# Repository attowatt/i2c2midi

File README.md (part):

# i2c2midi

### i2c2midi is a DIY open source 2 HP Teletype Expander that speaks I2C and MIDI.

i2c2midi bridges the gap between [monome Teletype](https://monome.org/docs/teletype/) and external MIDI-enabled devices. Using dedicated Teletype OPs, i2c2midi adds MIDI in and out to Teletype.

→ MIDI out:  
Sends MIDI notes, MIDI CC messages and other MIDI messages from Teletype to external devices like synths and effects.  

← MIDI in:  
Receives MIDI messages from external MIDI controllers and stores the values internally, which can be requested and used within Teletype.

- Dedicated Teletype OPs: `I2M.x`
- MIDI *out* via TRS
- MIDI *out* and *in* via USB Host
- Automatic MIDI Note Off messages (settable note duration per note)
- Chords and Chord Transformations
- Looping MIDI buffer / MIDI recorder
- Works with monome crow, too, thanks to [mreid](https://github.com/mreid/crow-i2c2midi)  
- 8 voice polyphony per MIDI channel, 16 channels simultaneously
- 2 HP, 42 mm depth

i2c2midi lines community thread:   
https://llllllll.co/t/i2c2midi-a-diy-module-that-translates-i2c-to-midi/

<br/>

<br/><br/>

## Table of contents
[Connections](#connections)  
[Example Scripts](#example-scripts)  
[Teletype OPs](#teletype-ops)   
[Further Reading](#further-reading)   
[Build the module](#build-the-module)  
[Firmware](#firmware)  
[crow Library](#crow-library)  
[Thanks](#thanks)  
[Sources](#sources)  

<br/><br/>

## Connections

### TRS

Use a TRS MIDI adapter (Type A) to connect a standard MIDI DIN cable to the TRS output of i2c2midi.

i2c2midi can be used with up to 16 different external MIDI-enabled devices simultaneously, with each device receiving MIDI messages on one of the 16 available MIDI channels. Just make sure each device is set to a different MIDI channel. Use a MIDI through splitter to connect all devices. Set the MIDI channel to 1..16 for the TRS output, using `I2M.CH`.

Please note: The TRS connection is MIDI *out* only!

### USB 

The USB connection can be used for either [MIDI *out*](#usb-midi-out-host) to connect an additional device (e.g. Teenage Engineering OP-1), or [MIDI *in*](#usb-midi-in-host) to receive MIDI Note or CC messages from an external MIDI controller.

Several MIDI controllers can be connected using a USB hub for MIDI *in*.

i2c2midi acts as a USB host, which makes it possible to connect external USB devices without the need of a computer. However, this also means that a computer (which acts as a host itself) can not be connected via the USB A jack on the front panel. However, it is possible to connect a USB host via the Micro USB jack of the Teensy. [More info about that here](#usb-midi-out-device-to-host).

#### USB MIDI out (Host)

The USB MIDI out connection works like the TRS output, but the 16 available MIDI channels can be addressed separately from TRS. Set the MIDI channel with `I2M.CH` to 17..32 for MIDI channels 1..16 on the USB connection. Please note: Only one USB device can be connected at a time.

#### USB MIDI in (Host)

If an external MIDI controller is connected via USB, incoming MIDI messages are stored internally in i2c2midi, and can be requested by Teletype at any time:

 - MIDI Note messages: The last eight notes and their velocities are stored in a rotating "note history". Each new received note gets added to the history and pushes the oldest note out. The notes and velocities can be requested with `I2M.Q.N` and `I2M.Q.V`.
 - MIDI CC messages: All values (127 controllers * 16 channels = 2032 values total) are stored and can be requested with `I2M.Q.CC`.

**Please note: Use external power or a powered USB hub!**

If you connect a MIDI device without its own power supply, use a powered USB hub with power supply in between i2c2midi and the MIDI device. This prevents too much current from being drawn from the Teensy and the voltage regulator on the PCB. I would advise to always use a powered USB hub in between – to be on the safe side. 

In case of OP-1, please turn off USB charging by pressing `shift` + `COM`, then `OPT` (T4), then turn the blue encoder to toggle USB charging off.

#### USB MIDI out (Device to Host)

i2c2midi can act as a USB device, too, if you want to connect a device that acts as a USB host (e.g. a computer). For this, you can use the Micro USB jack of the Teensy, which is accessible on the back of the module. Enable the `USB_DEVICE` feature flag in the firmware (look for `//#define USB_DEVICE` and remove the `//`). 
Most importantly: Cut the 5V pads on the Teensy! Otherwise you will damage your Teensy once you connect power from the modular and the host device on the USB port. For more info on why and how to cut the 5V pads, please follow [this link](https://www.pjrc.com/teensy/external_power.html).

**Please note: Don't connect power and USB at the same time!**

Caution: Do not connect power from the modular and the default USB port of the Teensy at the same time, unless you have cut the 5V pads on the Teensy!! Otherwise you will damage your Teensy. 

### LEDs

- The top LED lights up when MIDI messages are coming in.
- The bottom LED lights up when MIDI messages are going out.

<br/>

<br/><br/>

---

## Example Scripts

#### Play a random note
```
#1 
I2M.CH 1                // set channel to 1
I2M.N + 60 RND 24 127   // play note between 60 and 84
```

#### Play a V/Oct note using `VN`
```
#1
J N.B RRND 1 15         // random note from a scale in V/Oct
K VN J                  // convert the V/Oct value to MIDI note number
I2M.N + 60 K 127        // play note 
```

#### Define and play a chord
```
#1
I2M.C.CLR 1             // clear chord 1
I2M.C.ADD 1 0           // add relative note 0
I2M.C.ADD 1 3           // add relative note 3
I2M.C.ADD 1 7           // add relative note 7

#2
I2M.C.STR 1 100         // set strumming to 100
I2M.C.DIR 1 7           // set play direction to 7: Pingpong
I2M.C 1 60 127          // play chord 1 with rootnote 60 and velocity 127 (= 60,63,67)
```

#### Define a chord using reverse binary
```
#1
I2M.C.B 1 R10010001     // define chord: 1 means add, 0 means don't add = 0,3,7
I2M.C 1 60 127          // play chord 1 with rootnote 60 and velocity 127 (= 60,63,67)
```

#### Play chords stored in pattern 0
```
#1 
I2M.C.B 1 PN.NEXT 0     // define chord with next value in pattern 0
I2M.C 1 60 127          // play chord 1 with rootnote 60 and velocity 127

#Pattern 0
137                     // = R10010001    = 0,3,7
265                     // = R100100001   = 0,3,8
1064                    // = R00010100001 = 3,5,10
1060                    // = R00100100001 = 2,5,10
```

#### Use chord 2 as scale for a chord 1
```
#1
I2M.C.B 1 R100100011    // define chord 1 = 0,3,7,8 (alternatively use "393")
I2M.C.B 2 R10110101101  // define chord 2 = 0,2,3,5,7,8,10 (minor scale) (or "1453")
I2M.C.SC 1 2            // set chord 2 as scale for chord 1

#2
J WRP + J 1 0 7         // increment J and wrap around 0 and 7
I2M.C.STR 1 200         // set strumming for chord 1 to 200 ms
I2M.C.TRP 1 J           // transpose chord 1 by J
I2M.C 1 60 127          // play chord 1 with rootnote 60 and velocity 127
```

#### Send transformed chord notes to Just Friends or ER-301 

To Just Friends:
```
#I 
JF.MODE 1
JF.SHIFT N 0

#1
I2M.C.B 1 R100100011    // define chord 1 = 0,3,7,8
I2M.C.B 2 R10110101101  // define chord 2 = 0,2,3,5,7,8,10 (minor scale)
I2M.C.SC 1 2            // set chord 2 as scale for chord 1

#2
J WRP + J 1 0 4         // increment J and wrap around 4
I2M.C.DIS 1 J 2         // distort chord 1 by J at anchor point 2
I2M.C.VCUR 1 1 40 100   // set a linear (type 1) velocity curve from 40% to 100%

#3
EV 4: $ 2
J WRP + J 1 0 3         // increment J and wrap around chord length
X I2M.C.QN 1 0 J        // get chord note and store in X
Y I2M.C.QV 1 127 J      // get chord note velocity and store in Y
Z SCL 0 127 0 800 Y     // scale velocity from 0..127 to 0..800
JF.NOTE N X VV Z        // play on Just Friends
```

To ER-301:  

```
#3
J WRP + J 1 0 3                 // increment J and wrap around chord length
SC.CV 1 N I2M.C.QN 1 0 J        // send V/Oct to ER-301
SC.CV 2 VV I2M.C.QV 1 127 J     // send velocity to ER-301 (set Gain to 7.88)
SC.TR.P 1                       // send a trigger to ER-301 envelope
```

#### Query CC 1-4 and store values in Pattern 0
```
#1 
L 0 3: PN 0 I I2M.Q.CC + I 1
```

#### Query MIDI notes from controller

Arpeggiator that plays MIDI notes currently held down on a connected MIDI controller.  
CV 1 sends out the V/OCT and CV 2 sends out the velocity. 

```
#I
I2M.Q.LATCH 0           // setting to only store currently played MIDI notes

#M
$ 1

#1
J WRP + J 1 0 7         // counter from 0..7
CV 1 N - I2M.Q.N J 48   // query MIDI note number and subtract 4 octaves
CV 2 VV * 4 I2M.Q.V J   // query MIDI note velocity and scale to VV 0..508
```

---

## Teletype OPs

### Overview

| Type | OP                                             | Alias   | Channel-specific variant [(?)](#channel-specific-op-variants) | Function                    |
| ---- | ---------------------------------------------- | ------- | ----------------------------------------------------- | ----------------------------------- |
| get  | [I2M.CH](#i2mch)                               | I2M.#   |                                                       | Get current Channel                 |
|      | [I2M.CH channel](#i2mch)                       | I2M.#   |                                                       | Set current Channel                 |
| get  | [I2M.TIME](#i2mtime)                           | I2M.T   | [I2M.T# channel](#i2mt)                               | Get note duration                   |
|      | [I2M.TIME duration](#i2mtime)                  | I2M.T   | [I2M.T# channel duration](#i2mt)                      | Set note duration                   |
| get  | [I2M.SHIFT](#i2mshift)                         | I2M.S   | [I2M.S# channel](#i2ms)                               | Get note shift                      |
|      | [I2M.SHIFT semitones](#i2mshift)               | I2M.S   | [I2M.S# channel semitones](#i2ms)                     | Set note shift                      |
|      | [I2M.MIN note mode](#i2mmin)                   |         | [I2M.MIN# channel note mode](#i2mmin-1)               | Set minimum note                    |
|      | [I2M.MAX note mode](#i2mmax)                   |         | [I2M.MAX# channel note mode](#i2mmax-1)               | Set maximum note                    |
| get  | [I2M.REP](#i2mrep)                             |         | [I2M.REP# channel](#i2mrep-1)                         | Get note repetition                 |
|      | [I2M.REP repetitions](#i2mrep)                 |         | [I2M.REP# channel repetitions](#i2mrep-1)             | Set note repetition                 |
| get  | [I2M.RAT](#i2mrat)                             |         | [I2M.RAT# channel](#i2mrat-1)                         | Get note ratcheting                 |
|      | [I2M.RAT ratchets](#i2mrat)                    |         | [I2M.RAT# channel ratchets](#i2mrat-1)                | Set note ratcheting                 |
|      | [I2M.MUTE on/off](#i2mmute)                    |         | [I2M.MUTE# channel on/off](i2mmute-1)                 | Set channel mute state              |
|      | [I2M.SOLO on/off](#i2msolo)                    |         | [I2M.SOLO# channel on/off](i2msolo-2)                 | Set channel solo state              |
|      | [I2M.NOTE note velocity](#i2mnote)             | I2M.N   | [I2M.N# channel note velocity](#i2mn)                 | Send Note On                        |
|      | [I2M.NOTE.O note](#i2mnoteo)                   | I2M.NO  | [I2M.NO# channel note](#i2mno)                        | Send Note Off                       |
|      | [I2M.NT note velocity duration](#i2mnt)        |         | [I2M.NT# channel note velocity dur](#i2mnt-1)         | Send Note On with duration          |
|      | [I2M.CHORD chord rootnote velocity](#i2mchord) | I2M.C   | [I2M.C# channel chord rootnote vel](#i2mc)            | Play chord                          |
|      | [I2M.C.ADD chord note](#i2mcadd)               | I2M.C+  |                                                       | Add note to chord                   |
|      | [I2M.C.RM chord note](#i2mcrm)                 | I2M.C-  |                                                       | Remove note to chord                |
|      | [I2M.C.INS chord index note](#i2mcins)         |         |                                                       | Insert note at index                |
|      | [I2M.C.DEL chord index](#i2mcdel)              |         |                                                       | Delete note at index                |
|      | [I2M.C.SET chord index note](#i2mcset)         |         |                                                       | Set note at index                   |
|      | [I2M.C.B chord revbinary](#i2mcb)              |         |                                                       | Define chord using reverse binary   |
|      | [I2M.C.CLR chord](#i2mcclr)                    |         |                                                       | Clear chord                         |
| get  | [I2M.C.L chord](#i2mcl)                        |         |                                                       | Get chord length                    |
|      | [I2M.C.L chord length](#i2mcl)                 |         |                                                       | Set chord length                    |
|      | [I2M.C.SC chord1 chord2](#i2mcsc)              |         |                                                       | Set chord2 as scale for chord1      |
|      | [I2M.C.REV chord iterations](#i2mcrev)         |         |                                                       | Set chord reversal                  |
|      | [I2M.C.ROT chord iterations](#i2mcrot)         |         |                                                       | Set chord rotation                  |
|      | [I2M.C.TRP chord semitones](#i2mctrp)          |         |                                                       | Set chord transposition             |
|      | [I2M.C.DIS chord iter. anchorpoint](#i2mcdis)  |         |                                                       | Set chord distortion                |
|      | [I2M.C.REF chord iter. anchorpoint](#i2mcref)  |         |                                                       | Set chord reflection                |
|      | [I2M.C.INV chord iteration](#i2mcinv)          |         |                                                       | Set chord inversion                 |
|      | [I2M.C.STR chord ms](#i2mcstr)                 |         |                                                       | Set chord strumming                 |
|      | [I2M.C.VCUR chord curve start end](#i2mcvcur)  | I2M.V~  |                                                       | Set chord velocity curve            |
|      | [I2M.C.TCUR chord curve start end](#i2mctcur)  | I2M.T~  |                                                       | Set chord time curve                |
|      | [I2M.C.DIR chord direction](#i2mcdir)          |         |                                                       | Set chord play direction            |
|      | [I2M.C.QN chord rootnote index](#i2mcqn)       |         |                                                       | Query chord note at index           |
|      | [I2M.C.QV chord velocity index](#i2mcqv)       |         |                                                       | Query chord note velocity at index  |
|      | [I2M.B.R on/off](#i2mbr)                       |         |                                                       | Turn recording to buffer on/off     |
|      | [I2M.B.L length](#i2mbl)                       |         |                                                       | Set buffer length                   |
|      | [I2M.B.START offset](#i2mbstart)               |         |                                                       | Add offset to buffer start          |   
|      | [I2M.B.END offset](#i2mbend)                   |         |                                                       | Add a negative offset to buffer end | 
|      | [I2M.B.DIR direction](#i2mbdir)                |         |                                                       | Set buffer play direction           |    
|      | [I2M.B.SPE percent](#i2mbspe)                  |         |                                                       | Set buffer play speed               |
|      | [I2M.B.FB iterations](#i2mbfb)                 |         |                                                       | Iterations until velocity reaches 0 |
|      | [I2M.B.NSHIFT semitones](#i2mbnshift)          |         |                                                       | Set note shift                      |
|      | [I2M.B.VSHIFT velocity](#i2mbvshift)           |         |                                                       | Set velocity shift                  |
|      | [I2M.B.TSHIFT ms](#i2mbtshift)                 |         |                                                       | Set duration shift                  |
|      | [I2M.B.NOFF semitones](#i2mbnoff)              |         |                                                       | Set note offset                     |
|      | [I2M.B.VOFF velocity](#i2mbvoff)               |         |                                                       | Set velocity offset                 |
|      | [I2M.B.TOFF ms](#i2mbtoff)                     |         |                                                       | Set duration offset                 |
|      | [I2M.B.CLR](#i2mbclr)                          |         |                                                       | Clear the buffer                    |
|      | [I2M.B.MODE mode](#i2mbmode)                   |         |                                                       | Set buffer mode (Free, Tape)        |
|      | [I2M.CC controller value](#i2mcc)              |         | [I2M.CC# channel controller value](#i2mcc-1)          | Send CC                             |
|      | [I2M.CCV controller value](#i2mccv)            |         | [I2M.CCV# channel controller value](#i2mccv-1)        | Send CC with volt value             |
| get  | [I2M.CC.OFF controller](#i2mccoff)             |         | [I2M.CC.OFF# channel controller](#i2mccoff-1)         | Get CC offset                       |
|      | [I2M.CC.OFF controller offset](#i2mccoff)      |         | [I2M.CC.OFF# channel controller offset](#i2mccoff-1)  | Set CC offset                       |
| get  | [I2M.CC.SLEW controller](#i2mccslew)           |         | [I2M.CC.SLEW# channel controller](#i2mccslew-1)       | Get CC slew                         |
|      | [I2M.CC.SLEW controller ms](#i2mccslew)        |         | [I2M.CC.SLEW# channel controller ms](#i2mccslew-1)    | Set CC slew                         |
|      | [I2M.CC.SET controller value](#i2mccset)       |         | [I2M.CC.SET# channel controller value](#i2mccset-1)   | Send CC and ignore slew             |
|      | [I2M.NRPN msb lsb value](#i2mnrpn)             |         | [I2M.NRPN# channel msb lsb value](#i2mnrpn-1)         | Send NRPN                           |
| get  | [I2M.NRPN.OFF msb lsb](#i2mnrpnoff)            |         | [I2M.NRPN.OFF# channel msb lsb](#i2mnrpnoff-1)        | Get NRPN offset                     |
|      | [I2M.NRPN.OFF msb lsb offset](#i2mnrpnoff)     |         | [I2M.NRPN.OFF# channel msb lsb offset](#i2mnrpnoff-1) | Set NRPN offset                     |
| get  | [I2M.NRPN.SLEW msb lsb](#i2mnrpnslew)          |         | [I2M.NRPN.SLEW# channel msb lsb](#i2mnrpnslew-1)      | Get NRPN slew                       |
|      | [I2M.NRPN.SLEW msb lsb ms](#i2mnrpnslew)       |         | [I2M.NRPN.SLEW# channel msb lsb ms](#i2mnrpnslew-1)   | Set NRPN slew                       |
|      | [I2M.NRPN.SET msb lsb value](#i2mnrpnset)      |         | [I2M.NRPN.SET# value msb lsb value](#i2mnrpnset-1)    | Send NRPN and ignore slew           |
|      | [I2M.PRG program](#i2mprg)                     |         |                                                       | Send Program Change                 |
|      | [I2M.PB value](#i2mpb)                         |         |                                                       | Send Pitchbend                      |
|      | [I2M.AT value](#i2mat)                         |         |                                                       | Send Aftertouch                     |
|      | [I2M.CLK](#i2mclk)                             |         |                                                       | Send Clock                          |
|      | [I2M.START](#i2mstart)                         |         |                                                       | Send Clock Start                    |
|      | [I2M.STOP](#i2mstop)                           |         |                                                       | Send Clock Stop                     |
|      | [I2M.CONT](#i2mcont)                           |         |                                                       | Send Clock Continue                 |
| get  | [I2M.Q.CH](#i2mqch)                            |         |                                                       | Get current MIDI in Channel         |
|      | [I2M.Q.CH channel](#i2mqch)                    | I2M.Q.# |                                                       | Set current MIDI in Channel         |
|      | [I2M.Q.LATCH on/off](#i2mqlatch)               |         |                                                       | Turn latch on/off                   |
| get  | [I2M.Q.NOTE index](#i2mqnote)                  | I2M.Q.N |                                                       | Get x-last Note On                  |
| get  | [I2M.Q.VEL index](#i2mqvel)                    | I2M.Q.V |                                                       | Get x-last Velocity                 |
| get  | [I2M.Q.CC controller](#i2mqcc)                 |         |                                                       | Get CC value                        |
| get  | [I2M.Q.LCH](#i2mqlch)                          |         |                                                       | Get last MIDI in Channel            |
| get  | [I2M.Q.LN](#i2mqln)                            |         |                                                       | Get last MIDI in Note On            |
| get  | [I2M.Q.LV](#i2mqlv)                            |         |                                                       | Get last MIDI in Velocity           |
| get  | [I2M.Q.LO](#i2mqlo)                            |         |                                                       | Get last MIDI in Note Off           |
| get  | [I2M.Q.LC](#i2mqlc)                            |         |                                                       | Get last MIDI in Controller         |
| get  | [I2M.Q.LCC](#i2mqlcc)                          |         |                                                       | Get last MIDI in CC Value           |
|      | [I2M.PANIC](#i2mpanic)                         |         |                                                       | Don't panic!                        |

---

#### OP Name
`OP`  
`OP (set)`  
`Alias`    
Description  

---

### MIDI out: Settings
*Settings for outoing MIDI messages*  

#### I2M.CH
`I2M.CH`  
`I2M.CH x`  
`I2M.#`  

Get currently set MIDI channel / Set MIDI channel `x` (1..16 for TRS, 17..32 for USB) for MIDI out. Use MIDI channels 1-16 for TRS output, 17-32 for USB output. Default is `x = 1`.  

#### I2M.TIME
`I2M.TIME`  
`I2M.TIME x`  
`I2M.T`  

Get current note duration / Set note duration of MIDI notes to `x` ms (0..32767) for current channel. Based on note duration, i2c2midi will send a MIDI Note Off message automatically. Set `x = 0` to deactivate automatic Note Off messages. Default is `x = 100`.

#### I2M.T#
`I2M.T# ch`
`I2M.T# ch x`  

Get current note duration / Set note duration of MIDI notes to `x` ms (0..32767) for channel `ch` (0..32). Based on note duration, i2c2midi will send a MIDI Note Off message automatically. Set `x = 0` to deactivate automatic Note Off messages. Default is `x = 100`. Use `ch = 0` to set for all channels.

#### I2M.SHIFT
`I2M.SHIFT`  
`I2M.SHIFT x`  
`I2M.S`  

Get current transposition / Set transposition of MIDI notes to `x` semitones (-127..127) for current channel. Default is `x = 0`.  

#### I2M.S#
`I2M.S# ch`  
`I2M.S# ch x`  

Get current transposition / Set transposition of MIDI notes to `x` semitones (-127..127) for channel `ch` (0..32). Default is `x = 0`. Use `ch = 0` to set for all channels.  

#### I2M.MIN
`I2M.MIN x y`  

Set minimum note number of MIDI notes to `x` (0..127), using mode `y` (0..3), for current channel. Default is `x = 0` and `y = 0`. The following modes are available for notes lower than the minimum: 0) Ignore notes 1) Clamp notes 2) Fold back notes by one octave 3) Fold back notes by multiple octaves.  

#### I2M.MIN#
`I2M.MIN# ch x y`  

Set minimum note number of MIDI notes to `x` (0..127), using mode `y` (0..3), for channel `ch` (0..32). Default is `x = 0` and `y = 0`. The following modes are available for notes lower than the minimum: 0) Ignore notes 1) Clamp notes 2) Fold back notes by one octave 3) Fold back notes by multiple octaves. Use `ch = 0` to set for all channels.  

#### I2M.MAX
`I2M.MAX x y`  

Set maximum note number of MIDI notes to `x` (0..127), using mode `y` (0..3), for current channel. Default is `x = 0` and `y = 0`. The following modes are available for notes higher than the maximum: 0) Ignore notes 1) Clamp notes 2) Fold back notes by one octave 3) Fold back notes by multiple octaves. 

#### I2M.MAX#
`I2M.MAX# ch x y`  

Set maximum note number of MIDI notes to `x` (0..127), using mode `y` (0..3), for channel `ch` (0..32). Default is `x = 0` and `y = 0`. The following modes are available for notes higher than the maximum: 0) Ignore notes 1) Clamp notes 2) Fold back notes by one octave 3) Fold back notes by multiple octaves. Use `ch = 0` to set for all channels.  

#### I2M.REP
`I2M.REP`  
`I2M.REP x`  

Get current repetition / Set repetition of MIDI notes to `x` repetitions (1..127) for current channel. Set `x = 1` for no repetitions. Default is `x = 1`.  

#### I2M.REP#
`I2M.REP# ch`  
`I2M.REP# ch x`  

Get current repetition / Set repetition of MIDI notes to `x` repetitions (1..127) for channel `ch` (0..32). Set `x = 1` for no repetitions. Default is `x = 1`. Use `ch = 0` to set for all channels.  

#### I2M.RAT
`I2M.RAT`  
`I2M.RAT x`  

Get current ratcheting / Set ratcheting of MIDI notes to `x` ratchets (1..127) for current channel. Set `x = 1` for no ratcheting. Default is `x = 1`.  

#### I2M.RAT#
`I2M.RAT# ch`  
`I2M.RAT# ch x`  

Get current ratcheting / Set ratcheting of MIDI notes to `x` ratchets (1..127) for channel `ch` (0..32). Set `x = 1` for no ratcheting. Default is `x = 1`. Use `ch = 0` to set for all channels.  

#### I2M.MUTE
`I2M.MUTE x`  
  
Set mute state of current MIDI channel to `x`. If `x = 1` all outoing MIDI messages on that channel are muted. Default is `x = 0`.  

#### I2M.MUTE#
`I2M.MUTE# ch x`  
  
Set mute state of MIDI channel `ch` to `x`. If `x = 1` all outoing MIDI messages on that channel are muted. Default is `x = 0`. Use `ch = 0` to set for all channels.  

#### I2M.SOLO
`I2M.SOLO x`  

Set solo state of current MIDI channel to `x`. If `x = 1` all outoing MIDI messages on that channel are solod. Default is `x = 0`.  

#### I2M.SOLO#
`I2M.SOLO x`  

Set solo state of MIDI channel `ch` to `x`. If `x = 1` all outoing MIDI messages on that channel are solod. Default is `x = 0`. Use `ch = 0` to set for all channels.  

---

### MIDI out: Notes
*Send an individual MIDI note. Each note consists of a note number (pitch), velocity and duration. i2c2midi will take care of Note Off messages send an automatic Note Off message based on the set note duration. The note duration can be set globally via `I2M.TIME` or individually via `I2M.NT`.*  

#### I2M.NOTE
`I2M.NOTE x y`  
`I2M.N`  

Send MIDI Note On message for note number `x` (0..127) with velocity `y` (1..127) on current channel. A velocity of `0` will be treated as a MIDI Note Off message.  

#### I2M.N#
`I2M.N# ch x y`    

Send MIDI Note On message for note number `x` (0..127) with velocity `y` (1..127) on channel `ch` (1..32). A velocity of `0` will be treated as a MIDI Note Off message.

#### I2M.NOTE.O
`I2M.NOTE.O x`  
`I2M.NO`  

Send a manual MIDI Note Off message for note number `x` (0..127) on current channel. This can be used either before i2c2midi sends the automatic Note Off message (to stop the note from playing before its originally planned ending), or in combination with `I2M.TIME` set to `0` (in which case i2c2midi does not send automatic Note Off messages).

#### I2M.NO#
`I2M.NO# ch x`  

Send a manual MIDI Note Off message for note number `x` (0..127) on channel `ch` (1..32). This can be used either before i2c2midi sends the automatic Note Off message (to stop the note from playing before its originally planned ending), or in combination with `I2M.TIME` set to `0` (in which case i2c2midi does not send automatic Note Off messages).  

#### I2M.NT
`I2M.NT x y z`  

Send MIDI Note On message for note number `x` (0..127) with velocity `y` (1..127) and note duration `z` ms (0..32767) on current channel.   

#### I2M.NT#
`I2M.NT# ch x y z`  

Send MIDI Note On message for note number `x` (0..127) with velocity `y` (1..127) and note duration `z` ms (0..32767) on channel `ch` (1..32).    

---

### MIDI out: Chords
*Play a chord, consisting of multiple MIDI notes. Chords are basically groups of relative note numbers or pitches. One chord consists of up to eight notes defined via `I2M.C.ADD`, `I2M.C.RM`, `I2M.C.INS`, `I2M.C.DEL` or `I2M.C.SET`. The notes are defined relative to the root note which is specified when playing a chord via `I2M.C`. When a chord is played, the notes are sent out as individual MIDI notes in the order they are defined in the chord. If no note has been defined in the chord yet, no note will be played. 8 chords can be defined using their respective index 1..8.*

#### I2M.CHORD
`I2M.CHORD x y z`  
`I2M.C`  

Play chord `x` (1..8) with root note `y` (0..127) and velocity `z` (1..127) on current channel.  

#### I2M.C#
`I2M.C# ch x y z`  

Play chord `x` (1..8) with root note `y` (0..127) and velocity `z` (1..127) on channel `ch` (1..32).  

#### I2M.C.ADD
`I2M.C.ADD x y`  
`I2M.C+`  

Add note `y` (-127..127) to chord `x` (0..8), with `y` relative to the root note specified when playing a chord. E.g. add `0`, `4` and `7` to define a major triad. Or go more experimental, e.g. `-2`, `13`, `2`, `13`. Up to eight chords can be defined, with eight notes each. Use `x = 0` to add the note to all chords.  

#### I2M.C.RM
`I2M.C.RM x y`  
`I2M.C-`  

Remove note `y` (-127..127) from chord `x` (0..8). If the chord contains note `y` multiple times, the latest instance is removed. If the chord does not contain the note the message is simply ignored. Use `x = 0` to remove the note from all chords.  

#### I2M.C.INS
`I2M.C.INS x y z`  

Add note `z` (-127..127) to chord `x` (0..8) at index `y` (0..7), with `z` relative to the root note. Already defined notes at index `y` and higher are pushed to the right. Use `x = 0` to insert the note to all chords.  

#### I2M.C.DEL
`I2M.C.DEL x y`  

Delete note at index `y` (0..7) from chord `x` (0..8). Notes at index `y + 1` and higher are pushed to the left. If `y` is higher than the length of the chord, the message is ignored. Use `x = 0` to delete the note from all chords.  

#### I2M.C.SET
`I2M.C.SET x y z`  

Set note at index `y` (0..7) in chord `x` (0..8) to note `z` (-127..127), replacing what was defined earlier at this index. If `y` is higher than the length of the chord, the message is ignored. Use `x = 0` to set the note in all chords.  

#### I2M.C.B
`I2M.C.B x y`  

Clear and define chord `x` (0..8) using reverse binary notation (`R...`). Use `1` or `0` in order to include or exclude notes from the chord. E.g. use `x = R10001001` for `0,4,7` (major triad) or `x = R1000000100000001` for `0,7,15`. `y` can be a maximum of 16 digit long. Use `x = 0` to clear and define all chords.  

#### I2M.C.CLR
`I2M.C.CLR x`  

Clear chord `x` (0..8). Use `x = 0` to clear all chords.  

#### I2M.C.L
`I2M.C.L x`  
`I2M.C.L x y`  

Get current length / Set length of chord `x` (0..8) to `y` (1..8). The length of a chord changes automatically each time a note is added or removed. Values of `x` higher than number of actual defined notes are ignored. Already defined notes are not affected by setting the chord length, but won't be played if their index is outside of the set chord length. Use `x = 0` to set the length of all chords.  

#### I2M.C.SC
`I2M.C.SC x y`  

Set scale for chord `x` (0..8) based on chord `y` (0..8). Setting a scale for a chord comes in handy when using chord transformations that introduce new notes, like `I2M.C.TRP`, `I2M.C.DIS` or `I2M.C.REF`. Use `y = 0` to remove the scale. Use `x = 0` to set scale for all chords.    

→ [More info on how scales work on i2c2midi](#how-scales-work-on-i2c2midi)

#### I2M.C.REV
`I2M.C.REV x y`  

Set reversal of notes in chord `x` (0..8) to `y`. `y = 0` or an even number means not reversed, `y = 1` or an uneven number  means reversed. E.g. `y = 1` for chord `0,3,7` will lead to `7,3,0`. Default is `y = 0`. Use `x = 0` to set reversal all chords. 

  https://user-images.githubusercontent.com/76960718/170448152-c708c42d-ed18-4411-b0e5-6085a569185b.mp4

#### I2M.C.ROT
`I2M.C.ROT x y`  

Set rotation of notes in chord `x` (0..8) to `y` steps (-127..127). E.g. `y = 1` of chord `0,3,7` will lead to `3,7,0`, `y = 2` will lead to `7,0,3`, `y = -1` will lead to `7,0,3`. Default is `y = 0`. Use `x = 0` to set rotation for all chords.  

  https://user-images.githubusercontent.com/76960718/170448234-86cafa1e-8ecd-4612-9a84-febde5bead3d.mp4

#### I2M.C.TRP
`I2M.C.TRP x y`  

Set transposition of chord `x` (0..8) to `y` (-127..127). Transposition adds `y` to the note number of each note in the chord. Default is `y = 0`. Use `x = 0` to set transposition for all chords. This transformation introduces new notes to the chord – try it in combination with setting a scale.  

  https://user-images.githubusercontent.com/76960718/170448291-4766446c-830e-4b92-a609-74fe5c757047.mp4

#### I2M.C.DIS
`I2M.C.DIS x y z`  

Set distortion of chord `x` (0..8) to width `y` (-127..127) with anchor point `z` (0..16). Distortion adds `y+n` to the note number of each note in the chord. The anchor point influences the direction and amount (`n`) of the transformation. Default is `y = 0`. Use `x = 0` to set distortion for all chords. This transformation introduces new notes to the chord – try it in combination with setting a scale.  

  https://user-images.githubusercontent.com/76960718/170519200-57bbb0fd-a168-498a-873c-f39924235f2d.mp4

#### I2M.C.REF
`I2M.C.REF x y z`  

Set reflection of chord `x` (0..8) to `y` (-127..127) with anchor point `z` (0..16). The anchor point defines at which axis the chord gets reflected. Default is `y = 0`. Use `x = 0` to set distortion for all chords. This transformation introduces new notes to the chord – try it in combination with setting a scale.  

  https://user-images.githubusercontent.com/76960718/170448450-b01a0faa-ed1b-4541-b9ee-6c55721735cb.mp4

#### I2M.C.INV
`I2M.C.INV x y`  

Set inversion of chord `x` (0..8) to `y` (-32..32). Default is `y = 0`. Use `x = 0` to set inversion for all chords.  

  https://user-images.githubusercontent.com/76960718/170448519-62731788-977d-4e5f-a442-cc999a97c141.mp4

#### I2M.C.STR
`I2M.C.STR x y`  

Set strumming of chord `x` (0..8) to `y` ms (0..32767). Strumming plays the notes of a chord arpeggiated, with an interval of `y` ms in between notes. Default is `y = 0`. Use `x = 0` to set strumming for all chords.  

#### I2M.C.VCUR
`I2M.C.VCUR w x y z`  
`I2M.C.V~`  

Set velocity curve for chord `w` (0..8) with curve type `x` (0..5), start value `y`% (0..32767) and end value `z`% (0..32767). This will affect the velocity of the notes in the order they are defined in the chord. Start and end percentages refer to the velocity with which the chord is played via `I2M.C`. Use `x = 0` to turn velocity curve off. The following curves are available: 0) Off 1) Linear 2) Exponential 3) Triangle 4) Square 5) Random. Use `w = 0` to set velocity curve for all chords. Try a random curve with subtle values for a humanizing effect.  

#### I2M.C.TCUR
`I2M.C.TCUR w x y z`  
`I2M.C.T~`  

Set time curve for chord `w` (0..8) with curve type `x` (0..5), start value `y`% (0..32767) and end value `z`% (0..32767). This will affect the time interval between the notes in the order they are defined in the chord. Start and end percentages refer to the current strumming setting of the chord, set via `I2M.C.STR`. Use `x = 0` to turn time curve off. The following curves are available: 0) Off 1) Linear 2) Exponential 3) Triangle 4) Square 5) Random. Use `w = 0` to set time curve for all chords. Try a square curve with similar values to create swing. Try a random curve with subtle values for a humanizing effect.  

#### I2M.C.DIR
`I2M.C.DIR x y`   

Set play direction for chord `x` (0..8) to direction `y` (0..8). This will affect the order in which chord notes are played. Make sure to set strumming via `I2M.C.STR`. The following directions are available: 0) Forward (0,1,2,3,4) 1) Backward (4,3,2,1,0) 2) Inside out (2,1,3,0,4) 3) Outside in (0,4,1,3,2) 4) Random (2,3,1,0,4) 5) Bottom repeat (0,1,0,2,0,3,0,4) 6) Top repeat (0,4,1,4,2,4,3,4) 7) Pingpong (0,1,2,3,4,3,2,1,0) 8) Ping & pong (0,1,2,3,4,4,3,2,1,0). Default is `y = 0`.

#### I2M.C.QN
`I2M.C.QN x y z`   

Get the transformed note number of a chord note for chord `x` (1..8) with root note `y` (0..127) at index `z` (0..7). The reponse is the absolute note number (0..127). Use this OP to send the transformed note number to other devices within eurorack, e.g. via V/OCT to any oscillator or via I2C to I2C-enabled devices like Just Friends or disting EX.

#### I2M.C.QV
`I2M.C.QV x y z`   

Get the transformed note velocity of a chord note for chord `x` (1..8) with root velocity `y` (1..127) at index `z` (0..7). The response is the absolute note velocity (0..127). Use this OP to send the transformed note velocity to other devices within eurorack, e.g. via CV to a VCA or via I2C to I2C-enabled devices like Just Friends or disting EX.

---

### MIDI out: Buffer
*Record MIDI notes into a looping buffer. i2c2midi's MIDI buffer behaves much like a looping tape recorder, recording every MIDI note that leaves i2c2midi into the buffer. When the buffer reaches its end, it starts over and plays back the recorded notes, while new notes are recorded (overdubbed). Notes in the buffer can be modified with each buffer iteration. Change the note pitch via `I2M.B.NSHIFT` and `I2M.B.VSHIFT`, change note velocity via `I2M.B.FB`, `I2M.B.VSHIFT` and `I2M.B.VOFF`, change note duration via `I2M.B.TSHIFT` and `I2M.B.TOFF`. When notes reach a velocity of zero they get deleted from the buffer. However, notes can be held in the buffer indefinitely by setting `I2M.B.FB` to 0. Furthermore, the speed and playback direction of the buffer can be set, as well as the length and a start and end offset. The buffer can work in two modes, set via `I2M.B.MODE`.*   
*Depending on the settings, the buffer can act more like a MIDI looper or more like a pitch-shifting delay for MIDI notes.*  

#### I2M.B.R  
`I2M.B.R x`  

Turn recording of notes into the buffer on or off. `x = 1` is on, `x = 0` is off. If recording is turned on, all outgoing MIDI notes are recorded into the buffer, storing note number, note velocity, note duration and MIDI channel.  

#### I2M.B.L  
`I2M.B.L x`  

Set the length of the buffer to `x` ms (0..32767). Default is `x = 1000`.  

#### I2M.B.START  
`I2M.B.START x`  

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
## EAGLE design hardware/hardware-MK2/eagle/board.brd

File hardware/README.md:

# Build Guide

## I 
Get the parts. Here's the [BOM](https://github.com/attowatt/i2c2midi#BOM).

## II
- Solder the following parts:
  - Resistors (R1, R2, R3, R4, R5)
  - Voltage regulator: Bend the legs before soldering.
  - Power header: Please check the orientation – the opening of the header should be on the right, when -12V is on the bottom.
  - Capacitors: C1 (0.33 uF) negative side (white line, short leg) should be facing away from the power header. Orientation of C2 (0.1 uF) capacitor does not matter. 
  - I2C header
  - Teensy header: I prefer to solder a few pins with the Teensy board attached (to make sure it will fit later), then remove the Teensy and solder the rest of the pins.
- Cut the legs of the parts.

## III
- Mount the spacer to the PCB with one of the two M3 screws.
- Place the stereo jack (U1) and leds into their positions, but don't solder them yet.
- Place the panel on top of the stereo jack and spacer. Mount it to the jack with the nut and to the spacer with the second M3 screw.

## IV
- Carefully place the LEDs into position, so they look nice on the panel. Then solder them.
- Solder the stereo jack.

## V
Flash the firmware to the Teensy.
Don't connect the module to Euro power and USB at the same time! 

**Via Teensyduino**
- Download the firmware and open it with [Teensyduino](https://www.pjrc.com/teensy/td_download.html).
- Connect the Teensy to your computer with a USB cable.
- Under `Tools`, set `Board` to `Teensy 3.2`, `USB Type` to `Serial`, and select the `Port` that shows the Teensy.
- Upload the firmware to your Teensy via `Sketch` → `Upload`. 
- If the upload was successfull, i2c2midi lights up with both LEDs turning on and off four times.

**Via Teensy Loader** (not tested)
- Download and open the [Teensy Loader App](https://www.pjrc.com/teensy/loader.html).
- Connect the Teensy to your computer with a USB cable.
- Select `File` → `Open HEX File` and load the [HEX file of the firmware](../firmware/i2c2midi_firmware_v2_3/i2c2midi_firmware_v2_3.ino.hex).
- Select `Program`.
- If the upload was successfull, i2c2midi lights up with both LEDs turning on and off four times.

## Disclaimer:
After building the module, please test it very carefully in a separate case. This is a DIY module. I am not responsible for any damage to your gear.

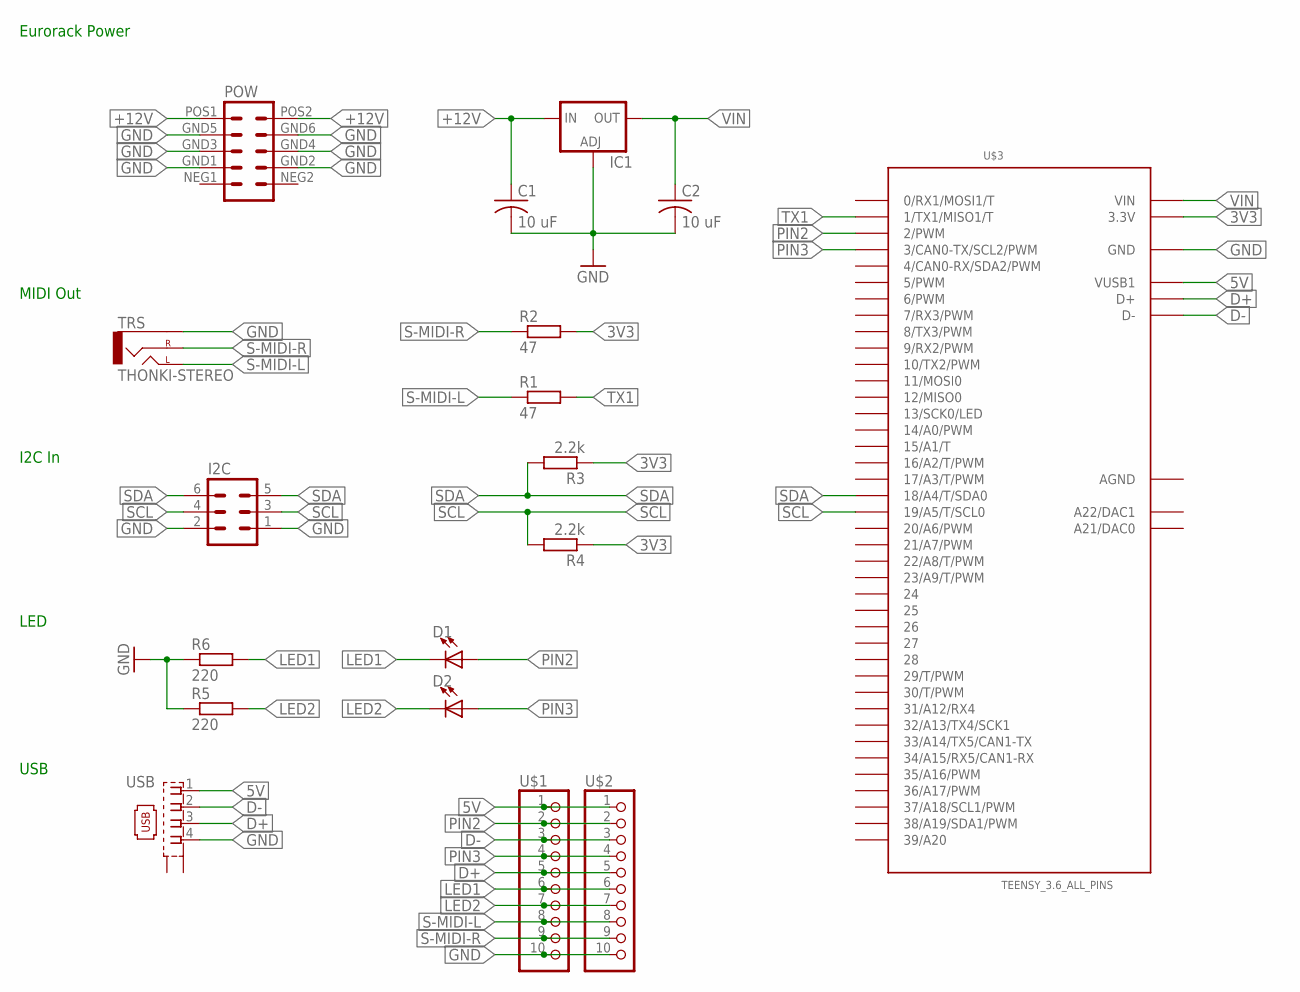
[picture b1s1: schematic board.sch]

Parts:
C1, C2: 10 uF; C050-025X075
D1, D2: LED3MM
I2C: MA03-2BACKSIDEFRONTSIDE; MA03-2
IC1: LD117AS50TR; SOT223
POW: EURO_POWER_HEADERLOCK_PADS; EURO_PWR_HEADER_LOCK
R1, R2: 47; 10MM_RESISTOR
R3, R4: 2.2k; 10MM_RESISTOR
R5, R6: 220; 10MM_RESISTOR
TRS: THONKI-STEREO; WQP-PJ366ST_JACK
U$1, U$2: PINHD-1X10; 1X10-BIG
U$3: TEENSY_3.6_ALL_PINS
USB: KUSBVX

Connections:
3V3: R2.2, R3.1, R4.1, U$3.3.3V, U$3.3.3V3 (3.3V)
5V: U$1.1, U$2.1, U$3.VUSB1, USB.1
+12V: C1.1, IC1.3 (IN), POW.POS1 (10), POW.POS2 (9)
AGND: U$3.AGND
D+: U$1.5, U$2.5, U$3.D+, USB.3
D-: U$1.3, U$2.3, U$3.D-, USB.2
GND: C1.2, C2.2, I2C.1, I2C.2, IC1.1 (ADJ), POW.GND1 (4), POW.GND2 (3), POW.GND3 (6), POW.GND4 (5), POW.GND5 (8), POW.GND6 (7), R5.1, R6.1, TRS.P$3_SLEEVE (SLEEVE), U$1.10, U$2.10, U$3.GND, U$3.GND1 (GND), U$3.GND3 (GND), U$3.GND4 (GND), USB.4
LED1: D1.K (C), R6.2, U$1.6, U$2.6
LED2: D2.K (C), R5.2, U$1.7, U$2.7
PIN2: D1.A, U$1.2, U$2.2, U$3.2 (2/PWM)
PIN3: D2.A, U$1.4, U$2.4, U$3.3 (3/CAN0-TX/SCL2/PWM)
S-MIDI-L: R1.1, TRS.P$1_TIP (LEFT), U$1.8, U$2.8
S-MIDI-R: R2.1, TRS.P$2_SWITCH (RIGHT), U$1.9, U$2.9
SCL: I2C.3, I2C.4, R4.2, U$3.19/A5 (19/A5/T/SCL0)
SDA: I2C.5, I2C.6, R3.2, U$3.18/A4 (18/A4/T/SDA0)
TX1: R1.2, U$3.1 (1/TX1/MISO1/T)
VIN: C2.1, IC1.2 (OUT), IC1.4 (OUT), U$3.VIN

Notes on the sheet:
Eurorack Power
MIDI Out
I2C In
LED
USB

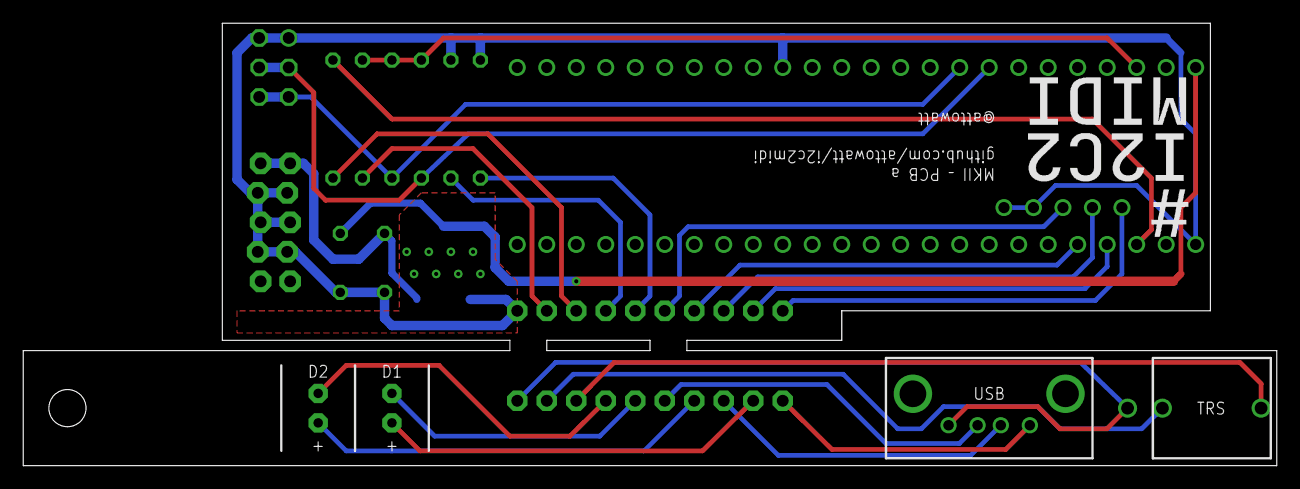
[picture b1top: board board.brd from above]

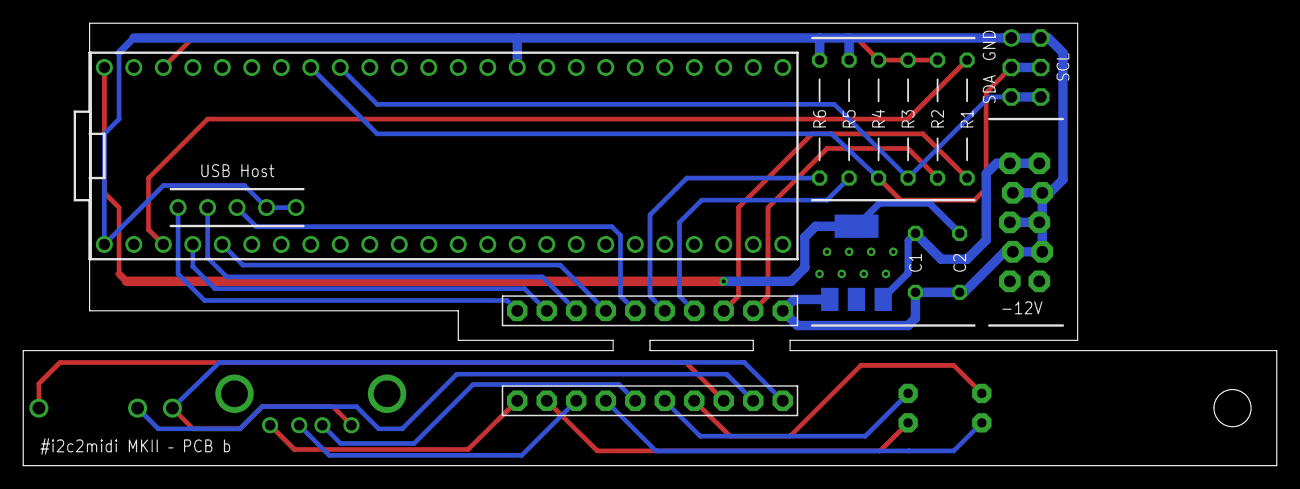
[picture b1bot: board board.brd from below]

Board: 2 copper layers, 108.0 x 38.1 mm, 18 parts (14 on the bottom side), 16 nets.

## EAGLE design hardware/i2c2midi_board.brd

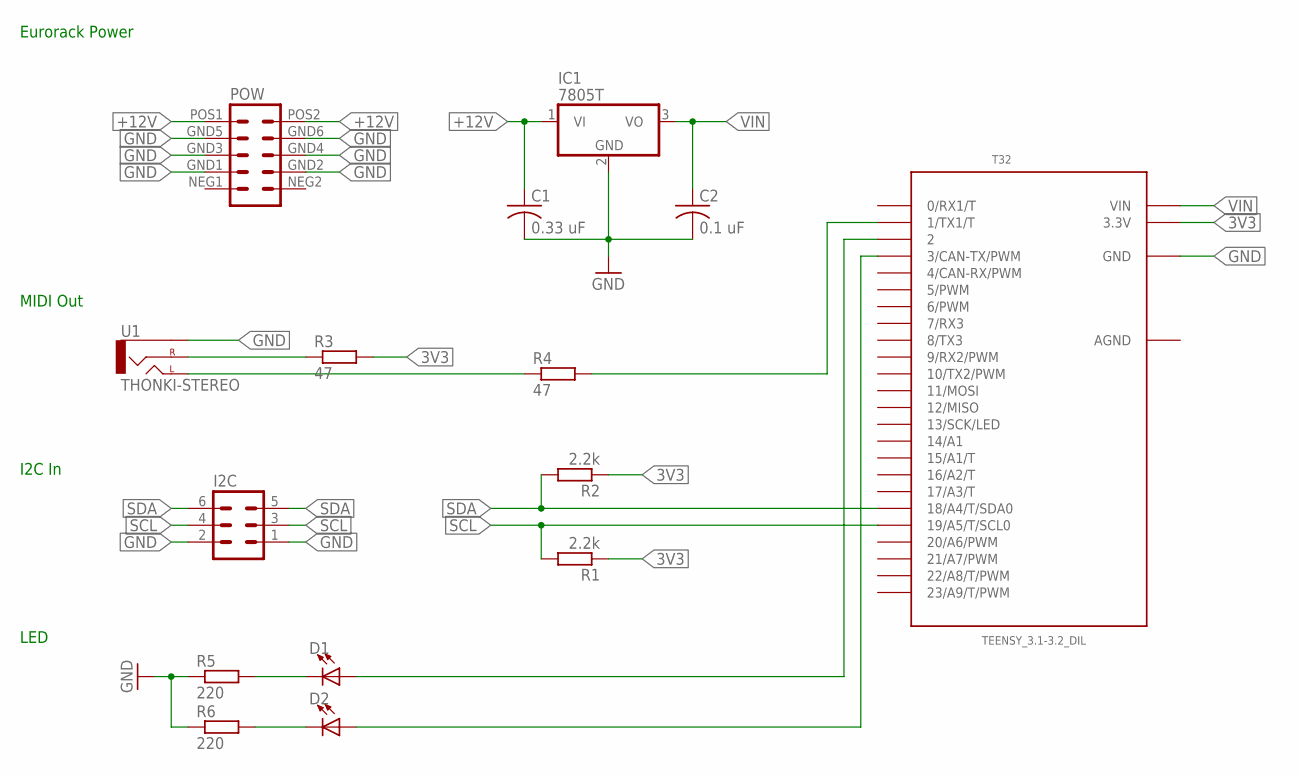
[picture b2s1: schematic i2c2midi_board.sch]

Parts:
C1: 0.33 uF; C050-025X075
C2: 0.1 uF; C050-025X075
D1, D2: LED3MM
I2C: MA03-2BACKSIDEFRONTSIDE; MA03-2
IC1: 7805T; TO220H
POW: EURO_POWER_HEADERLOCK_PADS; EURO_PWR_HEADER_LOCK
R1, R2: 2.2k; 10MM_RESISTOR
R3, R4: 47; 10MM_RESISTOR
R5, R6: 220; 10MM_RESISTOR
T32: TEENSY_3.1-3.2_DIL; TEENSY_3.0-3.2&LC_DIL
U1: THONKI-STEREO; WQP-PJ366ST_JACK

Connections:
3V3: R1.1, R2.1, R3.2, T32.3.3V
+12V: C1.1, IC1.1 (VI), POW.POS1 (10), POW.POS2 (9)
AGND: T32.AGND
GND: C1.2, C2.2, I2C.1, I2C.2, IC1.2 (GND), POW.GND1 (4), POW.GND2 (3), POW.GND3 (6), POW.GND4 (5), POW.GND5 (8), POW.GND6 (7), R5.1, R6.1, T32.GND, U1.P$3_SLEEVE (SLEEVE)
unnamed: R3.1, U1.P$2_SWITCH (RIGHT)
unnamed: D2.K (C), R6.2
unnamed: R4.2, T32.1 (1/TX1/T)
unnamed: R4.1, U1.P$1_TIP (LEFT)
unnamed: D1.K (C), R5.2
unnamed: D1.A, T32.2
unnamed: D2.A, T32.3 (3/CAN-TX/PWM)
SCL: I2C.3, I2C.4, R1.2, T32.19/A5 (19/A5/T/SCL0)
SDA: I2C.5, I2C.6, R2.2, T32.18/A4 (18/A4/T/SDA0)
VIN: C2.1, IC1.3 (VO), T32.VIN

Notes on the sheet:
Eurorack Power
MIDI Out
I2C In
LED

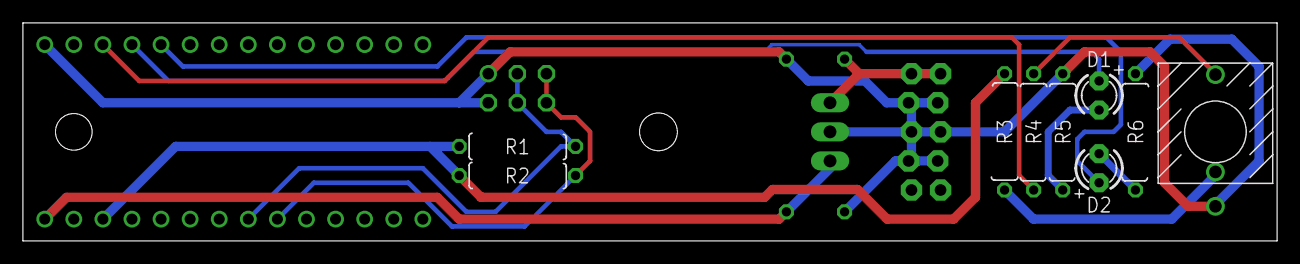
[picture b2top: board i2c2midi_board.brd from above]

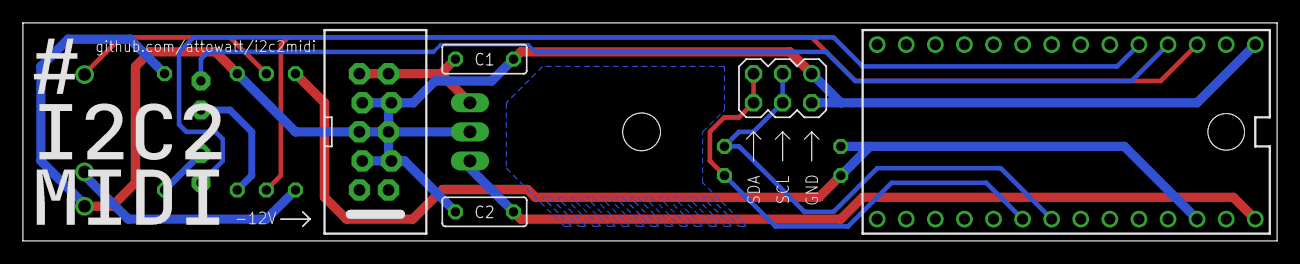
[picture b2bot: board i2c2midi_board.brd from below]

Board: 2 copper layers, 109.5 x 19.0 mm, 15 parts (6 on the bottom side), 13 nets.

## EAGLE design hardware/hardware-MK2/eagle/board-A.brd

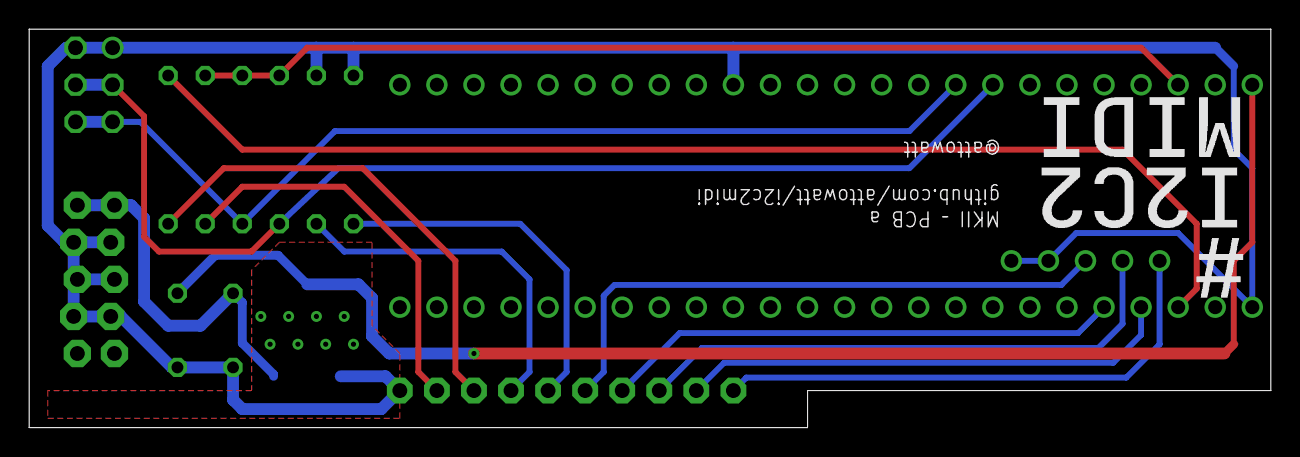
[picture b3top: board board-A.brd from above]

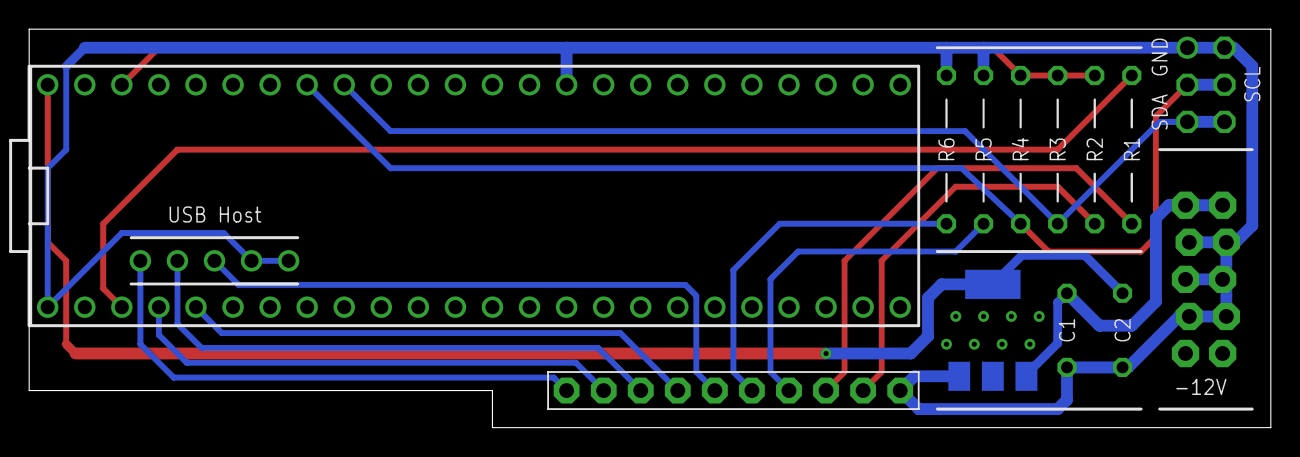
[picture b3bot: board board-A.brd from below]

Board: 2 copper layers, 85.1 x 27.3 mm, 13 parts (13 on the bottom side), 16 nets.

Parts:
C1, C2: 10 uF; C050-025X075
I2C: MA03-2
IC1: LD117AS50TR; SOT223
POW: EURO_POWER_HEADERLOCK_PADS; EURO_PWR_HEADER_LOCK
R1, R2: 47; 10MM_RESISTOR
R3, R4: 2.2k; 10MM_RESISTOR
R5, R6: 220; 10MM_RESISTOR
U$1: PINHD-1X10; 1X10-BIG
U$3: TEENSY_3.6_ALL_PINS

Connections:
3V3: R2.2, R3.1, R4.1, U$3.3.3V, U$3.3.3V3
5V: U$1.1, U$3.VUSB1
+12V: C1.1, IC1.3, POW.POS1, POW.POS2
D+: U$1.5, U$3.D+
D-: U$1.3, U$3.D-
GND: C1.2, C2.2, I2C.1, I2C.2, IC1.1, POW.GND1, POW.GND2, POW.GND3, POW.GND4, POW.GND5, POW.GND6, R5.1, R6.1, U$1.10, U$3.GND, U$3.GND1, U$3.GND3, U$3.GND4
LED1: R6.2, U$1.6
LED2: R5.2, U$1.7
PIN2: U$1.2, U$3.2
PIN3: U$1.4, U$3.3
S$16: R1.1, U$1.8
S-MIDI-R: R2.1, U$1.9
SCL: I2C.3, I2C.4, R4.2, U$3.19/A5
SDA: I2C.5, I2C.6, R3.2, U$3.18/A4
TX1: R1.2, U$3.1
VIN: C2.1, IC1.2, IC1.4, U$3.VIN

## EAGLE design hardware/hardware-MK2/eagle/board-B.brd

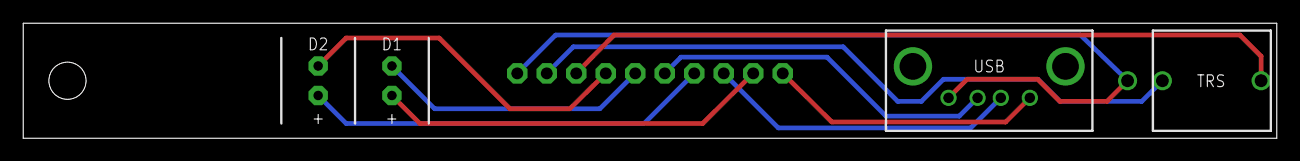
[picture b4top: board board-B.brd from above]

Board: 2 copper layers, 108.0 x 9.9 mm, 5 parts (1 on the bottom side), 10 nets.

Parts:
D1, D2: LED3MM
U1: THONKI-STEREO; WQP-PJ366ST_JACK
U$2: PINHD-1X10; 1X10-BIG
X1: KUSBVX

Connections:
D-: U$2.3, X1.2
GND: U1.P$3_SLEEVE, U$2.10, X1.4
LED1: D1.K, U$2.6
LED2: D2.K, U$2.7
PIN2: D1.A, U$2.2
PIN3: D2.A, U$2.4
S$21: U$2.1, X1.1
S$22: U$2.5, X1.3
S-MIDI-L: U1.P$1_TIP, U$2.8
S-MIDI-R: U1.P$2_SWITCH, U$2.9

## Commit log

2021-03-20 Delete hardware directory
    will be replaced by new layout
2021-03-20 Add files via upload
    new layout with voltage regulator
2021-03-28 Update README.md
    added MIDI TRS Type A Wiring info
2021-04-23 Rename README.md to buildGuide.md
2021-04-23 Rename buildGuide.md to README.md
2021-04-25 Rename i2c2midi_firmware.ino to i2c2midi_firmware_v2_0.ino
2021-04-25 Rename i2c2midi_firmware_v2_0.ino to i2c2midi_firmware_v2_0_1.ino
2021-04-25 added 8-voice polyphony, pitch bend, pgr change
2021-04-26 fixed a little mistake on the print layer
2021-04-26 Add files via upload
    Gerber Files
2021-04-26 Rename i2c2midi_firmware/i2c2midi_firmware_v2_0_1.ino to i2c2midi_firmware/i2c2midi_firmware_v2_0_1/i2c2midi_firmware_v2_0_1.ino
2021-04-26 Rename i2c2midi_firmware/i2c2midi_firmware_v2_3_0.ino to i2c2midi_firmware/i2c2midi_firmware_v2_3_0/i2c2midi_firmware_v2_3_0.ino
2021-04-26 Rename i2c2midi_firmware/i2c2midi_firmware_v2_0_1/i2c2midi_firmware_v2_0_1.ino to firmware/i2c2midi_firmware_v2_0_1/i2c2midi_firmware_v2_0_1.ino
2021-04-26 rename
2021-04-26 Renamed the file
2021-07-17 set i2c addres via EX.P 99; MIDI clock
2021-07-18 bugfix for MIDI clock functions
2021-08-30 Added optional USB MIDI support
2021-11-09 added midi clock out (delta time)
2021-11-09 fixed bugs
2021-11-09 Revert "added midi clock out (delta time)"
    This reverts commit 881e57c8a152d3b58f1ed8141a1c37a639d73b65.
2021-11-09 added hex
2021-12-19 Rename README.md to README_MKI.md
2021-12-19 Rename README_MKI.md to hardware/i2c2midi_hardware_MK1/README.md
2021-12-19 firmware for hardware MKII
2021-12-22 Update README.md
    added note about external power
2021-12-22 Added example scripts
2021-12-23 Added tested usb devices
2022-01-04 Fix description of TRS connection in README
2022-01-07 New pictures for Build Guide
2022-01-13 fixed a bug when sending midi note off via usb
2022-01-19 add hex file
2022-01-20 add note about 5V pad and Teensy Micro USB jack
2022-01-20 add hex
2022-01-20 bugfix: rename usb instance
2022-01-27 change file structure
2022-01-27 fix URLs in README
2022-01-27 add support for USB Device
2022-01-27 update comments
2022-01-27 update changelog
2022-01-27 add note about LED orientation in build guide
2022-01-27 change location of readme
2022-01-27 fix url in readme
2022-01-27 update build guide MKI
2022-01-27 change order of todos in step VI of the build guide
2022-01-27 add few updates to build guide
2022-01-27 add few updates to build guide II
2022-01-28 fix bug limit range of I2C requests commands
2022-01-29 add new example code
2022-01-31 refactored midi clock
    Midi clock now uses:
    uClock lib for sending 96PPQN,
    CircularBuffer for keeping a buffer of times to calculate BPM.
    Default set to 1/4 note;
    Teletype M 500 = 120 BPM
2022-03-20 add support for dedicated TT OPs
2022-03-20 add link to TT beta firmware
2022-03-20 add info about I2C address (`0x3F`)
2022-03-22 add hex files
2022-03-23 add note about pressing button on Teensy
2022-03-23 add new hex file for MK1
2022-03-27 bugfix I2M.C.L setter
2022-04-30 support Teensy 4.1 (experimental)
2022-05-04 experimental support for Teensy 4.1
2022-05-26 add firmware v 4.2
2022-05-26 add link to lines
2022-05-26 update videos
2022-05-26 upload new distortion video
2022-05-27 clean up
2022-06-02 make OPs linkable
2022-06-04 restructure for release v4.2.0
2022-06-04 fix bug where chord 8 would not work as scale
2022-06-10 restructure files
2022-06-10 update image paths
2022-06-10 update links in readme
2022-06-10 update file paths
2022-06-10 update release version
2022-06-11 add notes about firmware update
2022-08-30 add firmware v 4.3
2022-08-30 remove hex and TT beta files
2022-08-31 add example scripts to readme
2022-09-01 add note about CPU speed
2022-09-13 fix typo in readme
2022-09-18 add new OPs: I2M.C.QN & I2M.C.QV
2022-09-18 add doc for I2M.C.QN & I2M.C.QV
2022-09-18 add code example for I2M.C.QN / I2M.C.QV
2022-12-26 add detailed info about scales
2022-12-26 fix bug where chord 1 could not be used as scale
2023-02-14 add MIDI in example script
2023-04-03 add link to crow library
2023-04-10 refactor docs for #-OPs
2023-05-07 add I2M.MUTE/SOLO; flag for multiple usb out
2023-05-31 bugfixes for teensyduino 1.58
    - changed `>=` to `>` in `insertIntoChord`
    - fixed comparisons of differently signed types by casting
    - added return statement to end of `playChord`
2023-06-06 ad example script for usage of VN
2023-06-06 add example script for usage of VN
2023-06-10 add I2M.C.DCUR
2023-10-27 Update README.md
    add note about cutting the 5v pad to the firmware update instructions
2025-01-01 Update ops.ino
    Fixed the index for op_I2M_C_DEL and op_I2M_C_SET
2025-01-02 bump version number to v5_0_2, update readme
2025-01-02 add experimental support for disting EX ops
2025-01-02 bugfixing
2025-01-06 add eagle files for PCB
2025-06-12 initial
2025-07-07 bugfix led for USB MIDI
2025-08-19 bugfix for note I2M.T, I2M.REP, I2M.RAT

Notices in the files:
README.md:
MIT License – Copyright (c) 2016 Francois Best
MIT License – Copyright (c) 2013-2018, Brian (nox771 at gmail.com)
MIT License – Copyright 2017 Paul Stoffregen (paul@pjrc.com)
MIT License – Copyright © 2019-2020 Richard Gemmell
GPL-3.0 License – Sylvain GARNAVAULT - 2016/08/07
